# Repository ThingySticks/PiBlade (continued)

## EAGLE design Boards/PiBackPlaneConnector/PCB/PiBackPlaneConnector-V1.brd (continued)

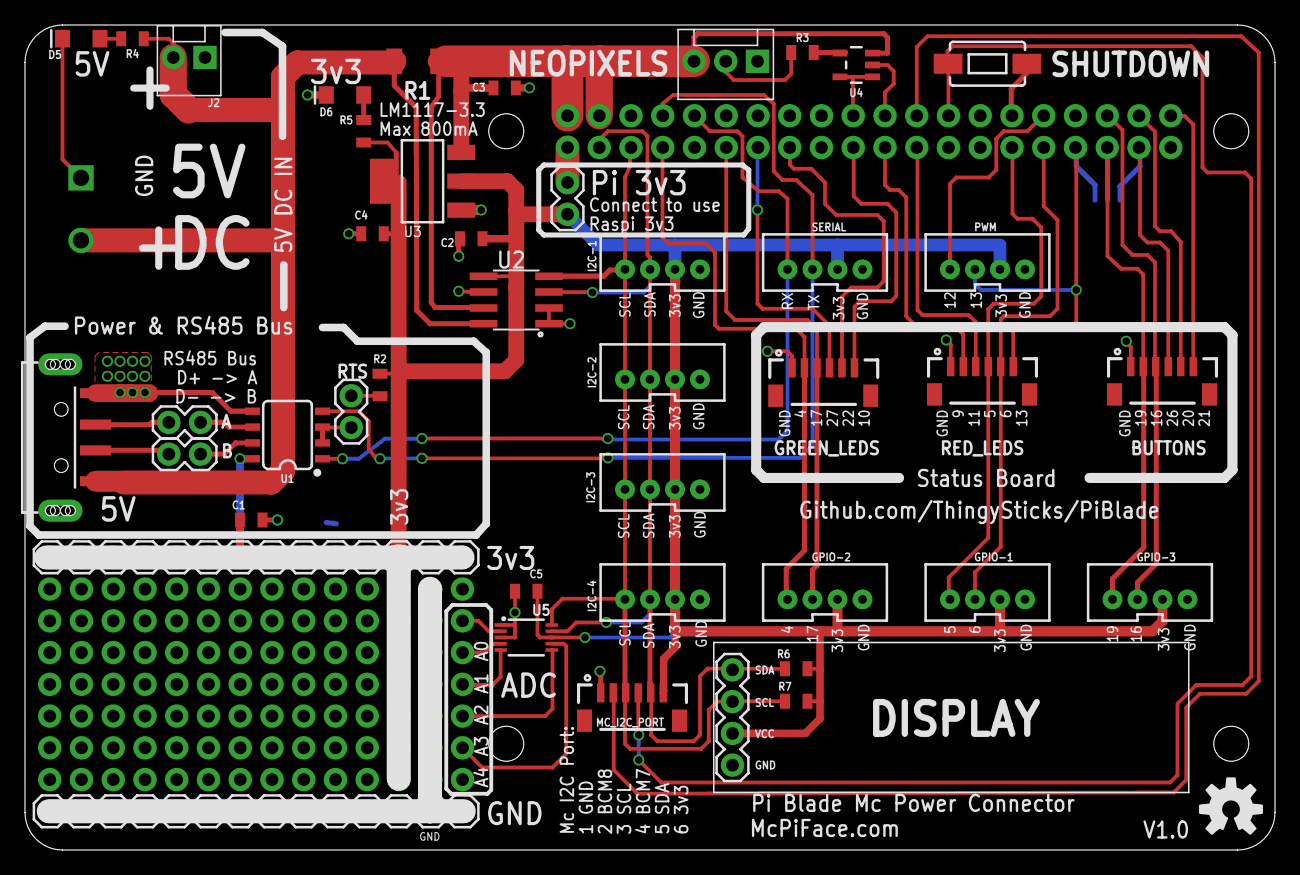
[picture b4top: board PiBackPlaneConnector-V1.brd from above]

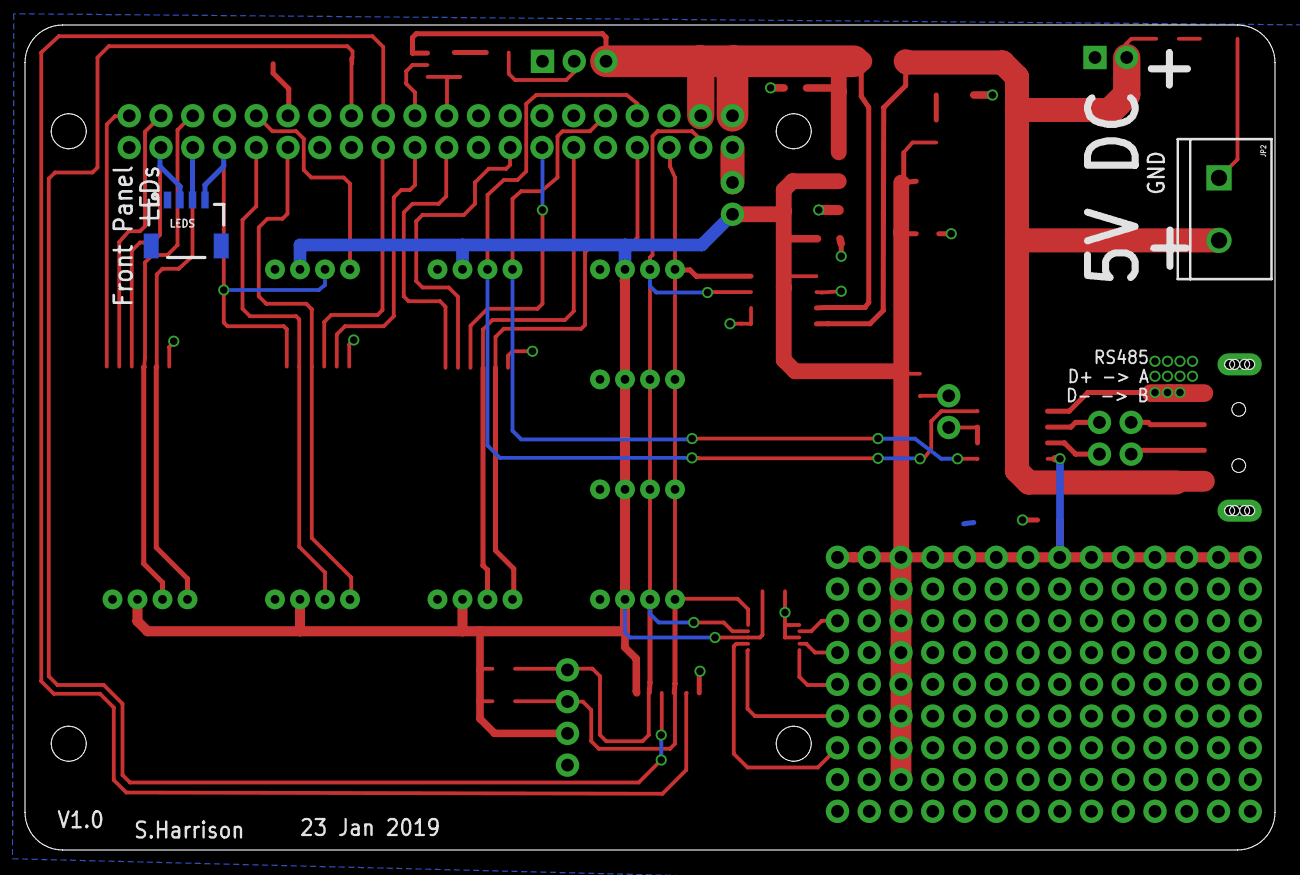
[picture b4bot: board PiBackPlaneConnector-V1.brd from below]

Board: 2 copper layers, 100.0 x 66.0 mm, 55 parts (3 on the bottom side), 43 nets.

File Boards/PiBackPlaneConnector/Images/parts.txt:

Partlist

Exported from PiBackPlaneConnector-V1.brd at 25/01/2019 11:44

EAGLE Version 7.4.0 Copyright (c) 1988-2015 CadSoft

Assembly variant: 

Part        Value                               Package                      Library                Position (mm)         Orientation

A                                               1X02                         SparkFun-Connectors    (-20.955 29.21)       R180
B                                               1X02                         SparkFun-Connectors    (-20.955 26.67)       R180
BUTTONS                                         1X06-1MM                     SparkFun-Connectors    (56 32.4)             R0
C1          0.1uF                               0805                         SparkFun-Capacitors    (-16.9 21.4)          R0
C2          0.1uF                               0805                         SparkFun-Capacitors    (0.7 43.9)            R180
C3          1.0uF                               0805                         SparkFun-Capacitors    (3.37 55.965)         R0
C4          0.1uF                               0805                         SparkFun-Capacitors    (-7.2 44.3)           R180
C5          0.1uF                               0805                         SparkFun-Capacitors    (5.1 15.7)            R180
D5          BLUE                                LED-1206                     SparkFun-LED           (-30.5 59.9)          R180
D6          BLUE                                LED-1206                     SparkFun-LED           (-9.4 55.4)           R180
DISPLAY     DISPLAY0.91_INCH_DISPLAY            I2C_DISPLAY_0.91_INCH        ThingySticks           (20.1 -0.4)           R0
GPIO-1                                          JST-4-PTH-VERT               SparkFun-Connectors    (42 15.6)             R0
GPIO-2                                          JST-4-PTH-VERT               SparkFun-Connectors    (29 15.6)             R0
GPIO-3                                          JST-4-PTH-VERT               SparkFun-Connectors    (55 15.6)             R0
GREEN_LEDS                                      1X06-1MM                     SparkFun-Connectors    (28.9 32.3)           R0
I2C-1                                           JST-4-PTH-VERT               SparkFun-Connectors    (16 42)               R0
I2C-2                                           JST-4-PTH-VERT               SparkFun-Connectors    (16 33.2)             R0
I2C-3                                           JST-4-PTH-VERT               SparkFun-Connectors    (16 24.4)             R0
I2C-4                                           JST-4-PTH-VERT               SparkFun-Connectors    (16 15.6)             R0
J1          CONN_20X2NOSILK                     2X20_NOSILK                  SparkFun-Connectors    (8.4 51.2)            R0
J2                                              MOLEX-1X2                    SparkFun-Connectors    (-20.6 58.4)          R180
J3                                              1X14                         SparkFun-Connectors    (-33.02 18.415)       R0
J4          USB_A_SMT_MALE                      USB-A-SMT-MALE               Tinamous               (-40.3 28)            R0
J7                                              1X02                         SparkFun-Connectors    (8.4 48.4)            R270
J8                                              1X14                         SparkFun-Connectors    (-33.02 -1.905)       R0
J9                                              1X14_NO_SILK                 SparkFun-Connectors    (-33.02 15.875)       R0
J10                                             1X14_NO_SILK                 SparkFun-Connectors    (-33.02 13.335)       R0
J11                                             1X14_NO_SILK                 SparkFun-Connectors    (-33.02 10.795)       R0
J12                                             1X14_NO_SILK                 SparkFun-Connectors    (-33.02 8.255)        R0
J13                                             1X14_NO_SILK                 SparkFun-Connectors    (-33.02 5.715)        R0
J14                                             1X14_NO_SILK                 SparkFun-Connectors    (-33.02 3.175)        R0
J15                                             1X14_NO_SILK                 SparkFun-Connectors    (-33.02 0.635)        R0
JP2                                             SCREWTERMINAL-5MM-2@1        SparkFun-Connectors    (-30.52 48.77)        MR270
LEDS                                            1X04_1MM_RA                  SparkFun-Connectors    (52.1 47)             MR0
MC_I2C_PORT                                     1X06-1MM                     SparkFun-Connectors    (13.6 6.3)            R0
NEOPIXELS                                       MOLEX-1X3                    SparkFun-Connectors    (23.6 58.1)           R180
PWM                                             JST-4-PTH-VERT               SparkFun-Connectors    (42 42)               R0
R1          0.1                                 1210                         SparkFun-Resistors     (-3.7 58.1)           R0
R2          10k                                 0805                         SparkFun-Resistors     (-6.6 32.2)           R90
R3                                              0805                         SparkFun-Resistors     (27.2 58.8)           R0
R4          1k5                                 0805                         SparkFun-Resistors     (-26.4 59.9)          R180
R5          1k                                  0805                         SparkFun-Resistors     (-7.9 52.5)           R90
R6          10k                                 0805                         SparkFun-Resistors     (26.7 9.5)            R180
R7          10k                                 0805                         SparkFun-Resistors     (26.7 6.9)            R180
RED_LEDS                                        1X06-1MM                     SparkFun-Connectors    (41.6 32.4)           R0
RTS                                             1X02                         SparkFun-Connectors    (-8.9 28.8)           R90
SERIAL                                          JST-4-PTH-VERT               SparkFun-Connectors    (29 42)               R0
SHUTDOWN    MOMENTARY-SWITCH-SPST-SMD-6.0X3.5MM TACTILE_SWITCH_SMD_6.0X3.5MM ThingySticks           (42 57.9)             R180
U1           MAX3485CSA                         SO08                         SparkFun-IC-Comms      (-14 28.2)            R90
U2          INA219AIDCNRSOIC                    SO08                         INA219AIDCNR           (4.3 39)              R90
U3                                              SOT223                       SparkFun-PowerIC       (-3.2 48.5)           R90
U4          SN74AHC1G125                        SOT23-5                      SparkFun-IC-Logic      (31.5 57.8)           R90
U5          ADS1015                             MSOP10                       SparkFun-IC-Conversion (5.1 12)              R270

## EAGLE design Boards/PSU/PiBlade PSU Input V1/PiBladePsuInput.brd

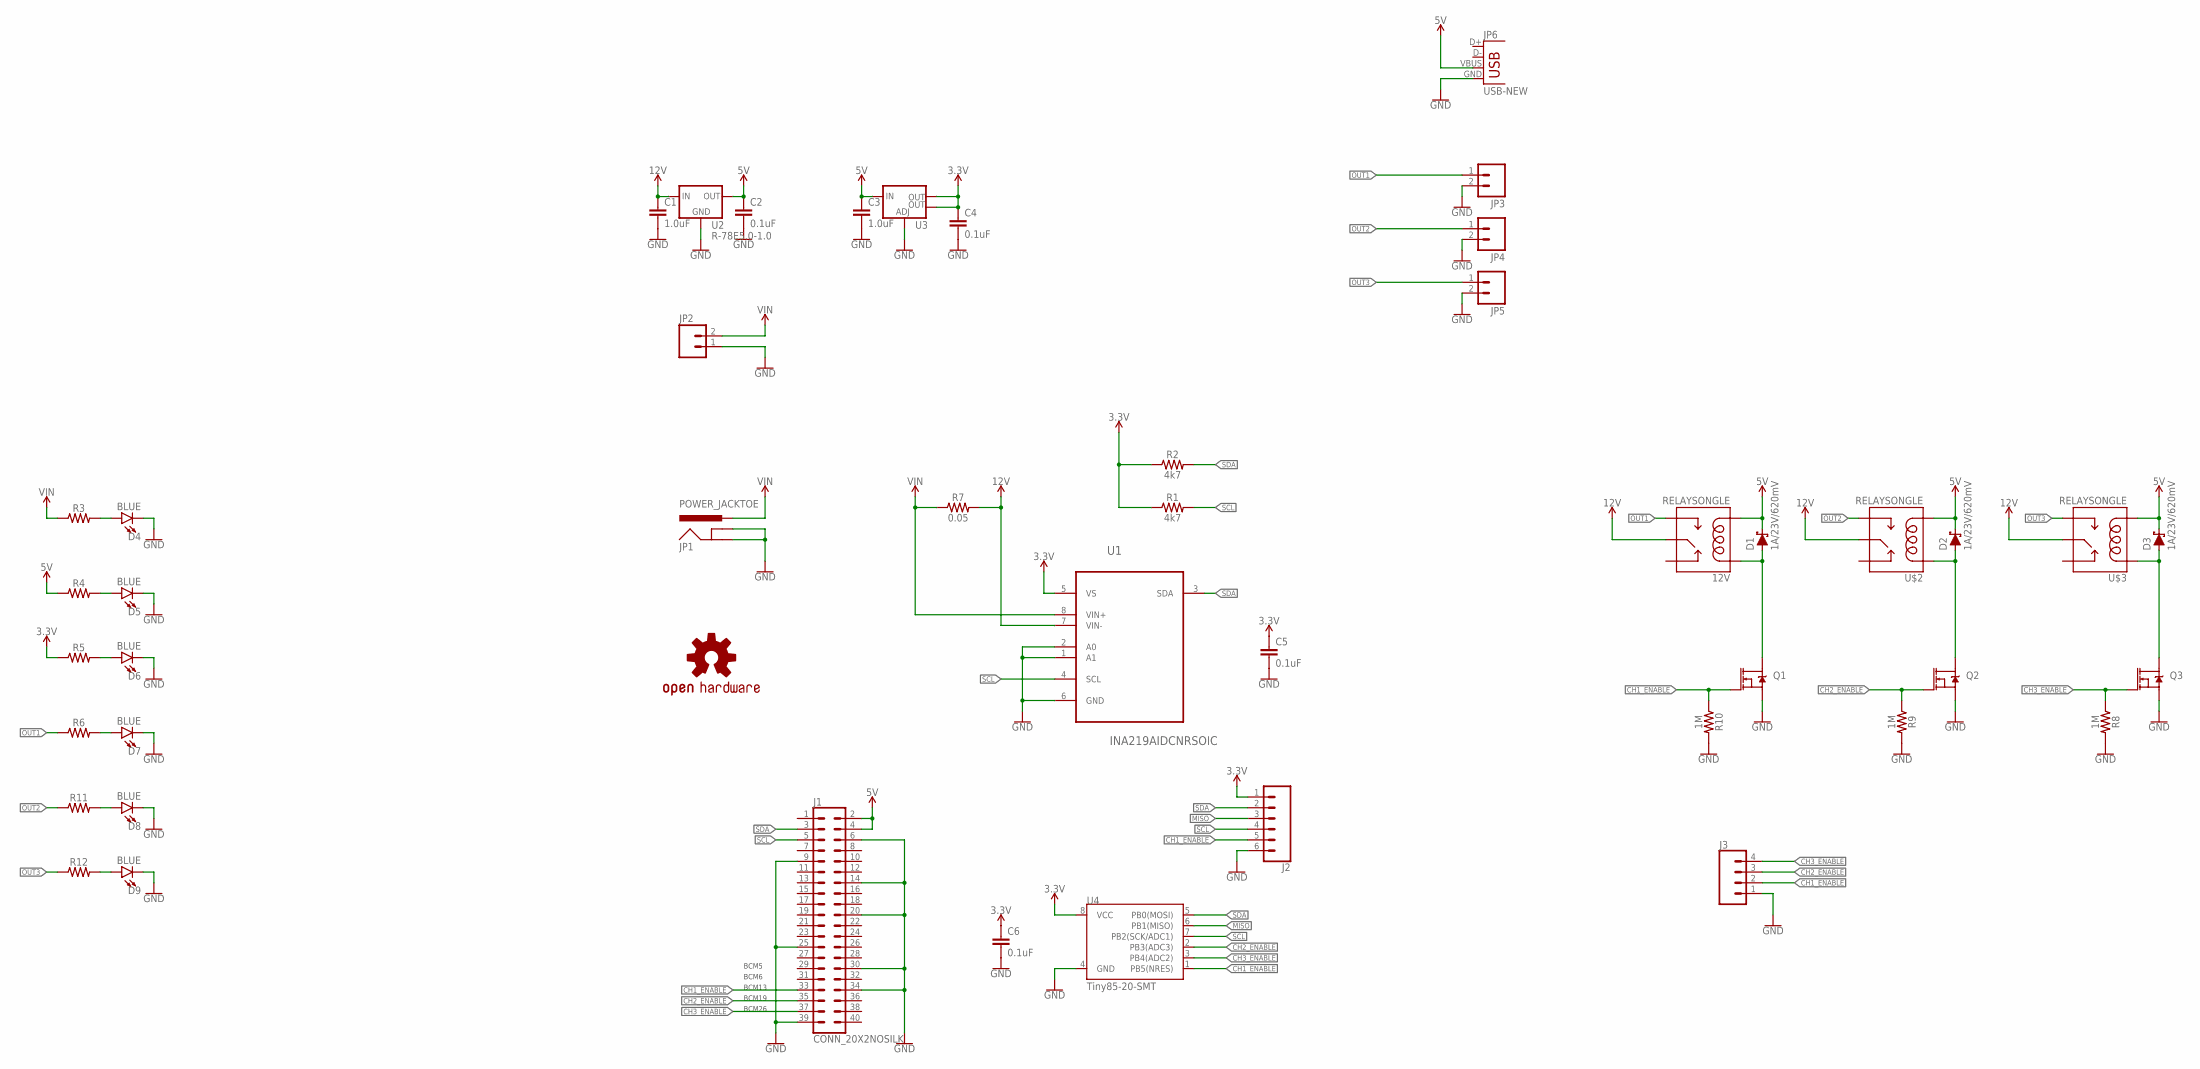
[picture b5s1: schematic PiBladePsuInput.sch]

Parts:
12V: RELAYSONGLE; SRD-5VDC-SL-C
C1, C3: 1.0uF; 0805
C2, C4, C5, C6: 0.1uF; 0805
D1, D2, D3: 1A/23V/620mV; SOD-323
D4, D5, D6, D7, D8, D9: BLUE; LED-1206
J1: CONN_20X2NOSILK; 2X20_NOSILK
J2: CONN_06SMD-1MM; 1X06-1MM
J3: CONN_04SMD2; 1X04_1MM_RA
JP1: POWER_JACKTOE; POWER_JACK_SMD_OVERPASTE_TOE
JP2, JP3, JP4, JP5: M025MM; SCREWTERMINAL-5MM-2
JP6: USB-NEW; USB-A-VERTICAL
LOGO1: OSHW-LOGOM; OSHW-LOGO-M
Q1, Q2, Q3: 220mA/50V/3.5Ω; SOT23-3
R1, R2: 4k7; 0805
R3, R4, R5, R6, R11, R12: 0805
R7: 0.05; 2512
R8, R9, R10: 1M; 0805
U1: INA219AIDCNRSOIC; SO08
U2: R-78E5.0-1.0; DC-DC_CONVERTER_78XX
U3: V_REG_LM1117SOT223; SOT223
U4: Tiny85-20-SMT; SO08-EIAJ
U$2, U$3: RELAYSONGLE; SRD-5VDC-SL-C

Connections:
3.3V: C4.1, C5.1, C6.1, J2.1, R1.1, R2.1, R5.1, U1.5 (VS), U3.2 (OUT), U3.4 (OUT), U4.8 (VCC)
5V: 12V.COIL2, C2.1, C3.1, D1.C, D2.C, D3.C, J1.2, J1.4, JP6.VBUS, R4.1, U2.VOUT (OUT), U3.3 (IN), U$2.COIL2, U$3.COIL2
12V: 12V.COMMON (MAIN), C1.1, R7.P$2 (2), U1.7 (VIN-), U2.VIN (IN), U$2.COMMON (MAIN), U$3.COMMON (MAIN)
CH1_ENABLE: J1.33, J2.5, J3.2, Q1.1 (G), R10.1, U4.1 (PB5(NRES))
CH2_ENABLE: J1.35, J3.3, Q2.1 (G), R9.1, U4.2 (PB3(ADC3))
CH3_ENABLE: J1.37, J3.4, Q3.1 (G), R8.1, U4.3 (PB4(ADC2))
GND: C1.2, C2.2, C3.2, C4.2, C5.2, C6.2, D4.C, D5.C, D6.C, D7.C, D8.C, D9.C, J1.6, J1.9, J1.14, J1.20, J1.25, J1.30, J1.34, J1.39, J2.6, J3.1, JP1.GND (GNDBREAK), JP1.P$4 (GND), JP2.1, JP3.2, JP4.2, JP5.2, JP6.GND, Q1.2 (S), Q2.2 (S), Q3.2 (S), R8.2, R9.2, R10.2, U1.1 (A1), U1.2 (A0), U1.6 (GND), U2.GND, U3.1 (ADJ), U4.4 (GND)
MISO: J2.3, U4.6 (PB1(MISO))
unnamed: D4.A, R3.2
unnamed: D6.A, R5.2
unnamed: D7.A, R6.2
unnamed: D5.A, R4.2
unnamed: D8.A, R11.2
unnamed: D9.A, R12.2
unnamed: D3.A, Q3.3 (D), U$3.COIL1
unnamed: D2.A, Q2.3 (D), U$2.COIL1
unnamed: 12V.COIL1, D1.A, Q1.3 (D)
OUT1: 12V.OPEN (NO), JP3.1, R6.1
OUT2: JP4.1, R11.1, U$2.OPEN (NO)
OUT3: JP5.1, R12.1, U$3.OPEN (NO)
SCL: J1.5, J2.4, R1.2, U1.4 (SCL), U4.7 (PB2(SCK/ADC1))
SDA: J1.3, J2.2, R2.2, U1.3 (SDA), U4.5 (PB0(MOSI))
VIN: JP1.VIN0 (PWR), JP2.2, R3.1, R7.P$1 (1), U1.8 (VIN+)

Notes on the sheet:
BCM13
BCM6
BCM5
BCM26
BCM19

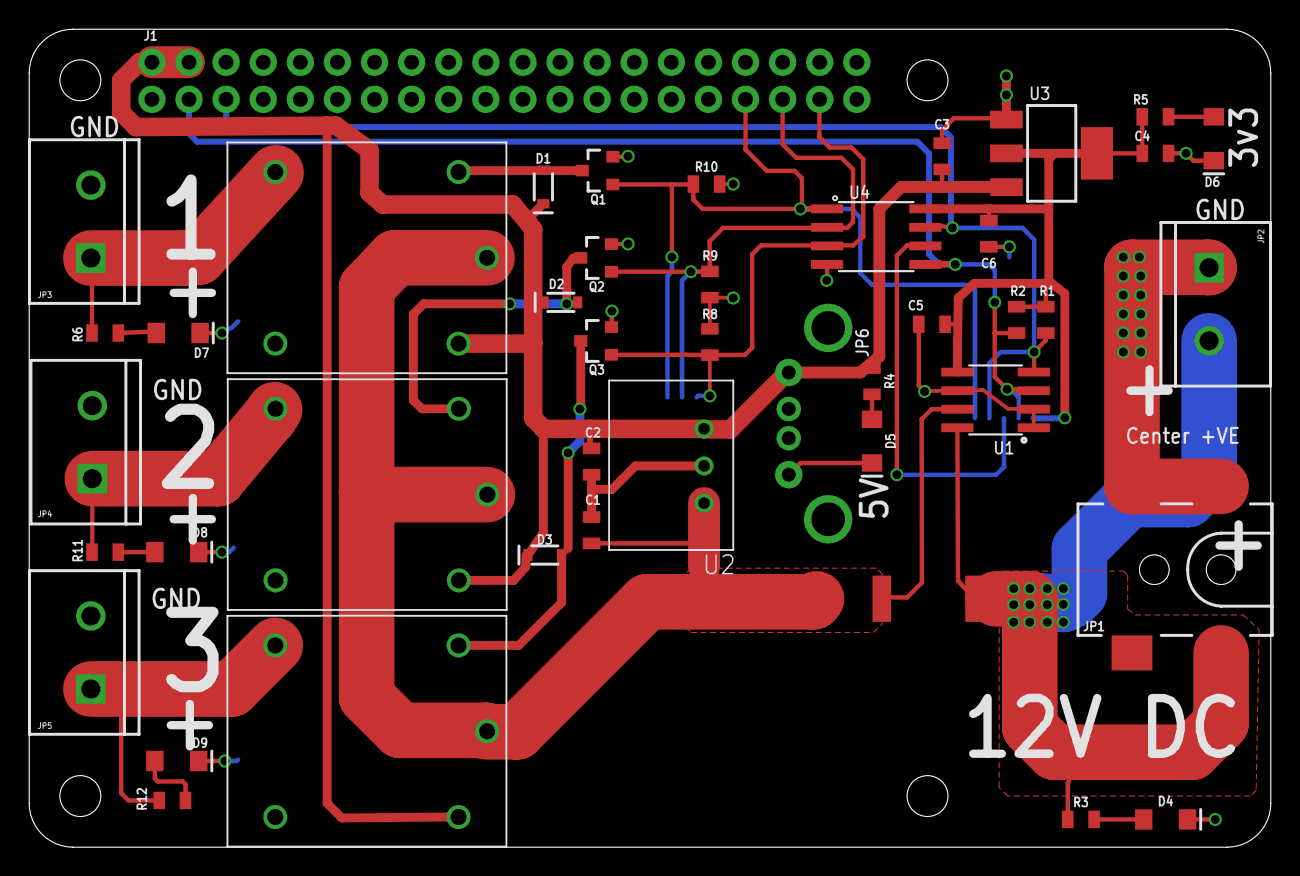
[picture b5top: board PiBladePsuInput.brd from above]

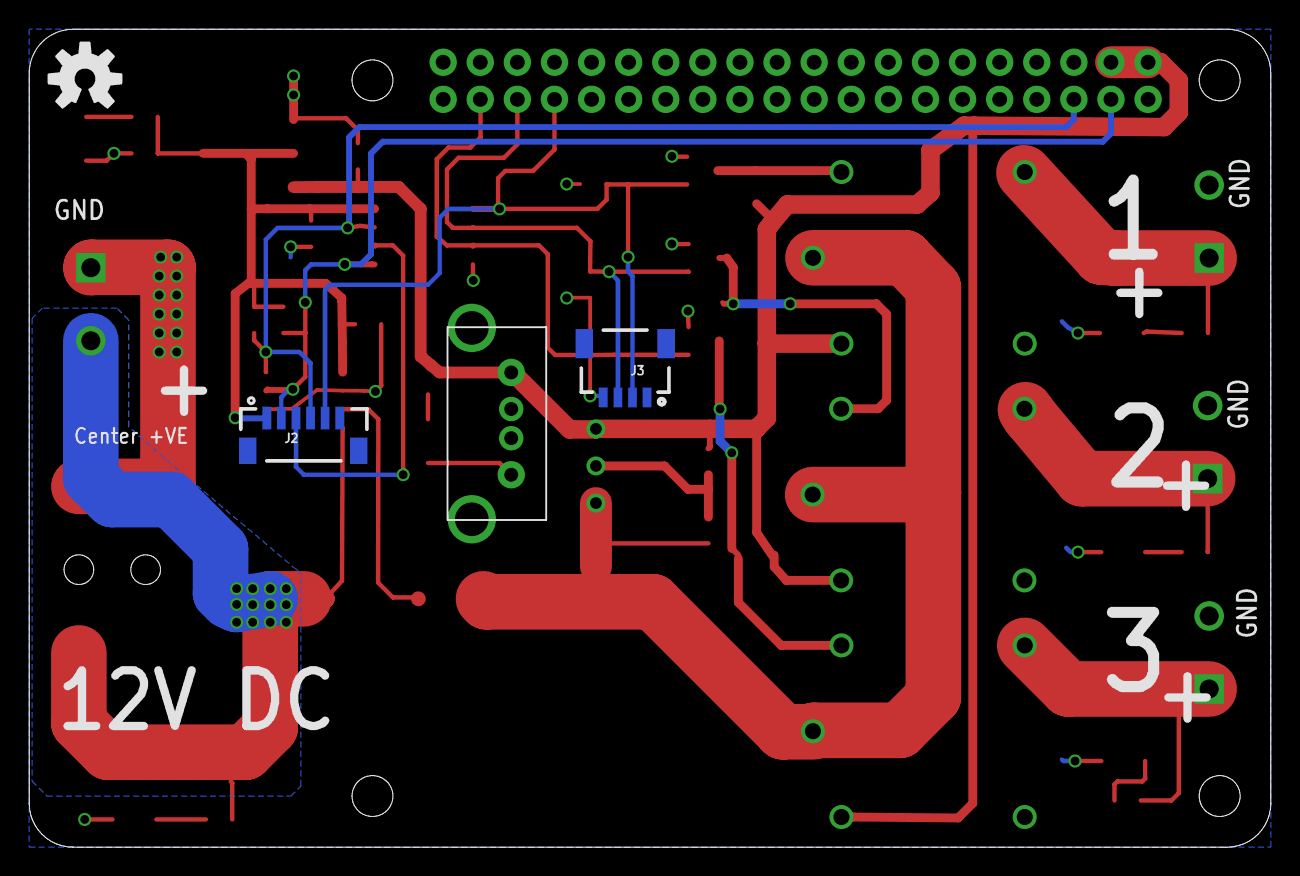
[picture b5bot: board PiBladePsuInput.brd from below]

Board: 2 copper layers, 85.0 x 56.0 mm, 47 parts (2 on the bottom side), 23 nets.

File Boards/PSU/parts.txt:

Partlist

Exported from PiBladePsuInput.brd at 25/01/2019 11:47

EAGLE Version 7.4.0 Copyright (c) 1988-2015 CadSoft

Assembly variant: 

Part     Value            Package                      Library               Position (mm)         Orientation

12V      RELAYSONGLE      SRD-5VDC-SL-C                ThingySticks          (23.12 40.35)         R0
C1       1.0uF            0805                         SparkFun-Capacitors   (38.5 21.7)           R90
C2       0.1uF            0805                         SparkFun-Capacitors   (38.5 26.4)           R270
C3       1.0uF            0805                         SparkFun-Capacitors   (62.5 47.3)           R90
C4       0.1uF            0805                         SparkFun-Capacitors   (77.1 47.5)           R0
C5       0.1uF            0805                         SparkFun-Capacitors   (61.8 35.8)           R180
C6       0.1uF            0805                         SparkFun-Capacitors   (65.7 42)             R270
D1       1A/23V/620mV     SOD-323                      SparkFun-DiscreteSemi (35.2 45.2)           R90
D2       1A/23V/620mV     SOD-323                      SparkFun-DiscreteSemi (36.4 37.3)           R0
D3       1A/23V/620mV     SOD-323                      SparkFun-DiscreteSemi (35.3 20)             R0
D4       BLUE             LED-1206                     SparkFun-LED          (77.8 1.9)            R0
D5       BLUE             LED-1206                     SparkFun-LED          (57.7 27.8)           R270
D6       BLUE             LED-1206                     SparkFun-LED          (81.1 48.5)           R270
D7       BLUE             LED-1206                     SparkFun-LED          (10.2 35.2)           R0
D8       BLUE             LED-1206                     SparkFun-LED          (10.1 20.2)           R0
D9       BLUE             LED-1206                     SparkFun-LED          (10.1 5.9)            R0
J1       CONN_20X2NOSILK  2X20_NOSILK                  SparkFun-Connectors   (8.4 51.2)            R0
J2                        1X06-1MM                     SparkFun-Connectors   (66.2 28.1)           MR0
J3                        1X04_1MM_RA                  SparkFun-Connectors   (44.2 30.8)           MR180
JP1      POWER_JACKTOE    POWER_JACK_SMD_OVERPASTE_TOE SparkFun-Connectors   (81.6 19)             R180
JP2                       SCREWTERMINAL-5MM-2          SparkFun-Connectors   (80.78 39.67)         R270
JP3                       SCREWTERMINAL-5MM-2          SparkFun-Connectors   (4.22 40.33)          R90
JP4                       SCREWTERMINAL-5MM-2          SparkFun-Connectors   (4.32 25.23)          R90
JP5                       SCREWTERMINAL-5MM-2          SparkFun-Connectors   (4.22 10.83)          R90
JP6      USB-NEW          USB-A-VERTICAL               Tinamous              (54.7 29)             R180
Q1       220mA/50V/3.5?   SOT23-3                      SparkFun-DiscreteSemi (38.96 46.32)         R90
Q2       220mA/50V/3.5?   SOT23-3                      SparkFun-DiscreteSemi (38.86 40.34)         R90
Q3       220mA/50V/3.5?   SOT23-3                      SparkFun-DiscreteSemi (38.86 34.66)         R90
R1       4k7              0805                         SparkFun-Resistors    (69.6 36.1)           R270
R2       4k7              0805                         SparkFun-Resistors    (67.6 36.1)           R270
R3                        0805                         SparkFun-Resistors    (72 1.9)              R0
R4                        0805                         SparkFun-Resistors    (57.7 31.9)           R270
R5                        0805                         SparkFun-Resistors    (77.1 50)             R0
R6                        0805                         SparkFun-Resistors    (5.2 35.2)            R0
R7       0.05             2512                         SparkFun-Resistors    (61.54 17.01)         R180
R8       1M               0805                         SparkFun-Resistors    (46.6 34.59)          R90
R9       1M               0805                         SparkFun-Resistors    (46.6 38.52)          R270
R10      1M               0805                         SparkFun-Resistors    (46.37 45.4)          R0
R11                       0805                         SparkFun-Resistors    (5.2 20.2)            R0
R12                       0805                         SparkFun-Resistors    (9.8 3.2)             R0
U$2      RELAYSONGLE      SRD-5VDC-SL-C                ThingySticks          (23.14 24.14)         R0
U$3      RELAYSONGLE      SRD-5VDC-SL-C                ThingySticks          (23.12 7.94)          R0
U1       INA219AIDCNRSOIC SO08                         INA219AIDCNR          (66.16 30.62)         R90
U2       R-78E5.0-1.0     DC-DC_CONVERTER_78XX         SparkFun-IC-Power     (46.2 26.1)           R90
U3                        SOT223                       SparkFun-PowerIC      (70 47.5)             R270
U4       Tiny85-20-SMT    SO08-EIAJ                    SparkFun-DigitalIC    (58 41.8)             R270

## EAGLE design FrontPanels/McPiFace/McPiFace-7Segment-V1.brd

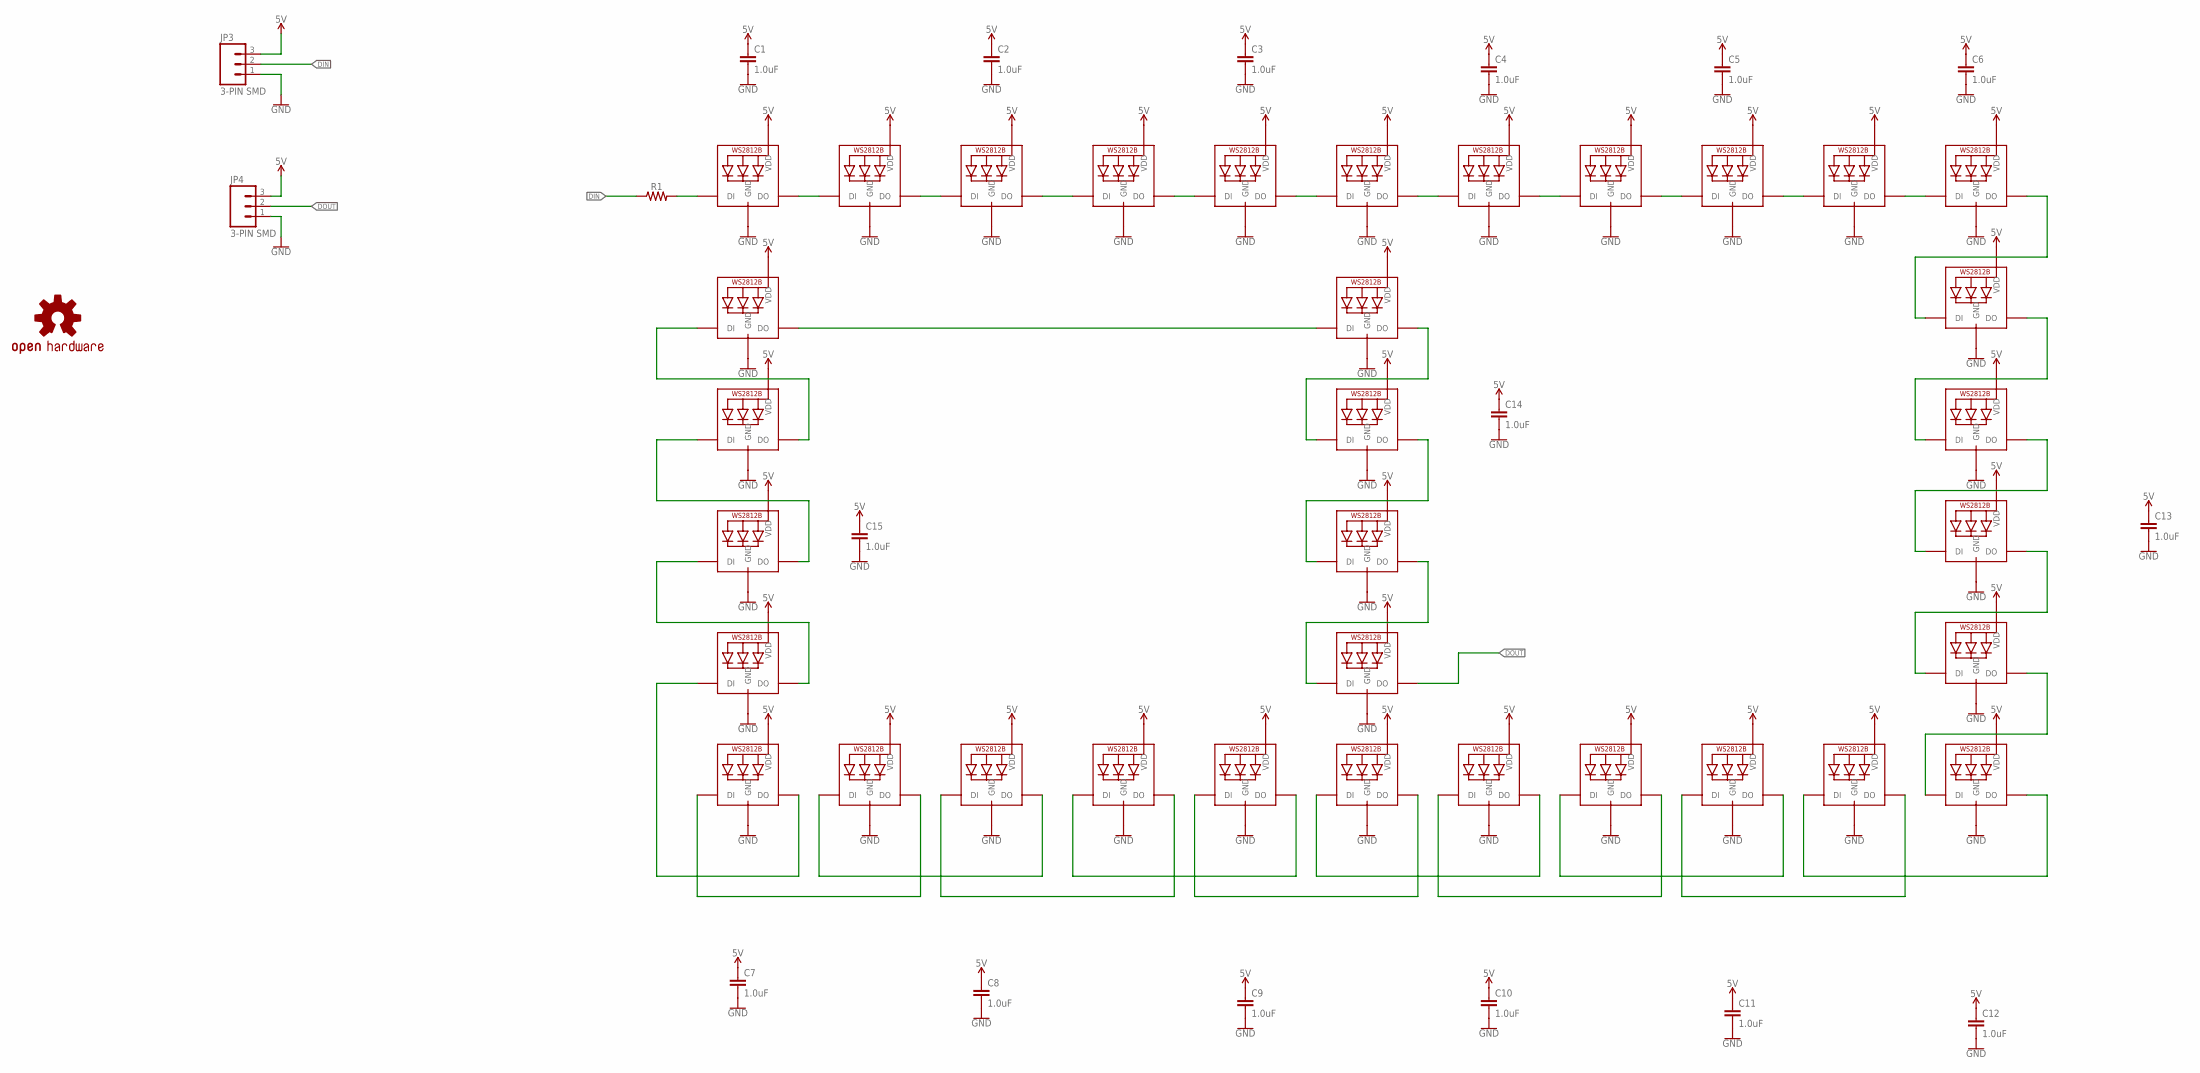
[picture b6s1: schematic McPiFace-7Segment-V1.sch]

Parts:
C1, C2, C3, C4, C5, C6, C7, C8, C9, C10, C11, C12, C13, C14, C15: 1.0uF; 0805-CAP
JP3, JP4: 3-PIN SMD; JST-3-SMD
LED1, LED2, LED3, LED4, LED5, LED6, LED7, LED8, LED9, LED10, LED11, LED12, LED13, LED14, LED15, LED16, LED17, LED18, LED19, LED20, LED21, LED22, LED23, LED24, LED25, LED26, LED27, LED28, LED29, LED30, LED31, LED32, LED33, LED34: WS2812B5050; WS2812B
LOGO1: OSHW-LOGOL; OSHW-LOGO-L
R1: 0805

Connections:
5V: C1.1, C2.1, C3.1, C4.1, C5.1, C6.1, C7.1, C8.1, C9.1, C10.1, C11.1, C12.1, C13.1, C14.1, C15.1, JP3.3, JP4.3, LED1.1-VDD (VDD), LED2.1-VDD (VDD), LED3.1-VDD (VDD), LED4.1-VDD (VDD), LED5.1-VDD (VDD), LED6.1-VDD (VDD), LED7.1-VDD (VDD), LED8.1-VDD (VDD), LED9.1-VDD (VDD), LED10.1-VDD (VDD), LED11.1-VDD (VDD), LED12.1-VDD (VDD), LED13.1-VDD (VDD), LED14.1-VDD (VDD), LED15.1-VDD (VDD), LED16.1-VDD (VDD), LED17.1-VDD (VDD), LED18.1-VDD (VDD), LED19.1-VDD (VDD), LED20.1-VDD (VDD), LED21.1-VDD (VDD), LED22.1-VDD (VDD), LED23.1-VDD (VDD), LED24.1-VDD (VDD), LED25.1-VDD (VDD), LED26.1-VDD (VDD), LED27.1-VDD (VDD), LED28.1-VDD (VDD), LED29.1-VDD (VDD), LED30.1-VDD (VDD), LED31.1-VDD (VDD), LED32.1-VDD (VDD), LED33.1-VDD (VDD), LED34.1-VDD (VDD)
DIN: JP3.2, R1.1
DOUT: JP4.2, LED15.2-DOUT (DO)
GND: C1.2, C2.2, C3.2, C4.2, C5.2, C6.2, C7.2, C8.2, C9.2, C10.2, C11.2, C12.2, C13.2, C14.2, C15.2, JP3.1, JP4.1, LED1.3-GND (GND), LED2.3-GND (GND), LED3.3-GND (GND), LED4.3-GND (GND), LED5.3-GND (GND), LED6.3-GND (GND), LED7.3-GND (GND), LED8.3-GND (GND), LED9.3-GND (GND), LED10.3-GND (GND), LED11.3-GND (GND), LED12.3-GND (GND), LED13.3-GND (GND), LED14.3-GND (GND), LED15.3-GND (GND), LED16.3-GND (GND), LED17.3-GND (GND), LED18.3-GND (GND), LED19.3-GND (GND), LED20.3-GND (GND), LED21.3-GND (GND), LED22.3-GND (GND), LED23.3-GND (GND), LED24.3-GND (GND), LED25.3-GND (GND), LED26.3-GND (GND), LED27.3-GND (GND), LED28.3-GND (GND), LED29.3-GND (GND), LED30.3-GND (GND), LED31.3-GND (GND), LED32.3-GND (GND), LED33.3-GND (GND), LED34.3-GND (GND)
unnamed: LED1.2-DOUT (DO), LED2.4-DIN (DI)
unnamed: LED1.4-DIN (DI), R1.2
unnamed: LED2.2-DOUT (DO), LED3.4-DIN (DI)
unnamed: LED3.2-DOUT (DO), LED4.4-DIN (DI)
unnamed: LED4.2-DOUT (DO), LED5.4-DIN (DI)
unnamed: LED5.2-DOUT (DO), LED6.4-DIN (DI)
unnamed: LED6.2-DOUT (DO), LED7.4-DIN (DI)
unnamed: LED7.2-DOUT (DO), LED8.4-DIN (DI)
unnamed: LED8.2-DOUT (DO), LED9.4-DIN (DI)
unnamed: LED9.2-DOUT (DO), LED10.4-DIN (DI)
unnamed: LED10.2-DOUT (DO), LED11.4-DIN (DI)
unnamed: LED11.2-DOUT (DO), LED17.4-DIN (DI)
unnamed: LED17.2-DOUT (DO), LED18.4-DIN (DI)
unnamed: LED18.2-DOUT (DO), LED19.4-DIN (DI)
unnamed: LED19.2-DOUT (DO), LED20.4-DIN (DI)
unnamed: LED20.2-DOUT (DO), LED21.4-DIN (DI)
unnamed: LED21.2-DOUT (DO), LED22.4-DIN (DI)
unnamed: LED22.2-DOUT (DO), LED23.4-DIN (DI)
unnamed: LED23.2-DOUT (DO), LED24.4-DIN (DI)
unnamed: LED24.2-DOUT (DO), LED25.4-DIN (DI)
unnamed: LED16.4-DIN (DI), LED25.2-DOUT (DO)
unnamed: LED16.2-DOUT (DO), LED26.4-DIN (DI)
unnamed: LED26.2-DOUT (DO), LED27.4-DIN (DI)
unnamed: LED27.2-DOUT (DO), LED28.4-DIN (DI)
unnamed: LED28.2-DOUT (DO), LED29.4-DIN (DI)
unnamed: LED29.2-DOUT (DO), LED30.4-DIN (DI)
unnamed: LED30.2-DOUT (DO), LED31.4-DIN (DI)
unnamed: LED31.2-DOUT (DO), LED32.4-DIN (DI)
unnamed: LED32.2-DOUT (DO), LED33.4-DIN (DI)
unnamed: LED33.2-DOUT (DO), LED34.4-DIN (DI)
unnamed: LED12.4-DIN (DI), LED34.2-DOUT (DO)
unnamed: LED12.2-DOUT (DO), LED13.4-DIN (DI)
unnamed: LED13.2-DOUT (DO), LED14.4-DIN (DI)
unnamed: LED14.2-DOUT (DO), LED15.4-DIN (DI)

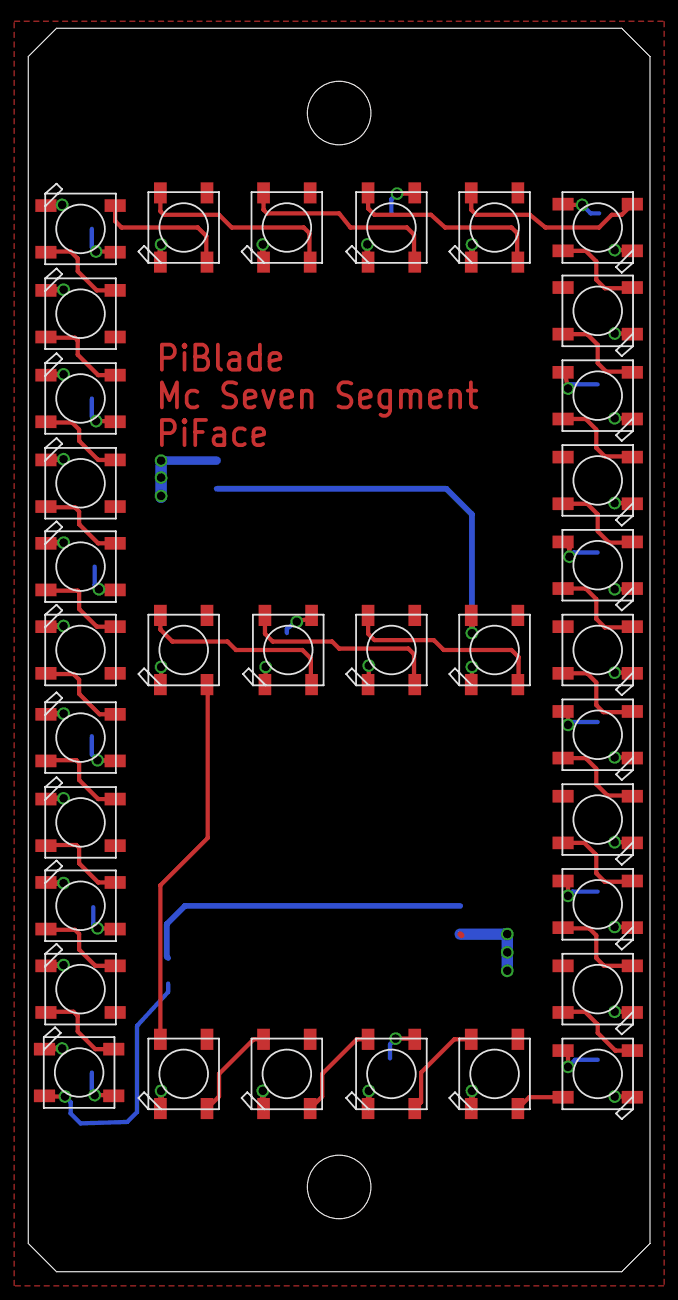
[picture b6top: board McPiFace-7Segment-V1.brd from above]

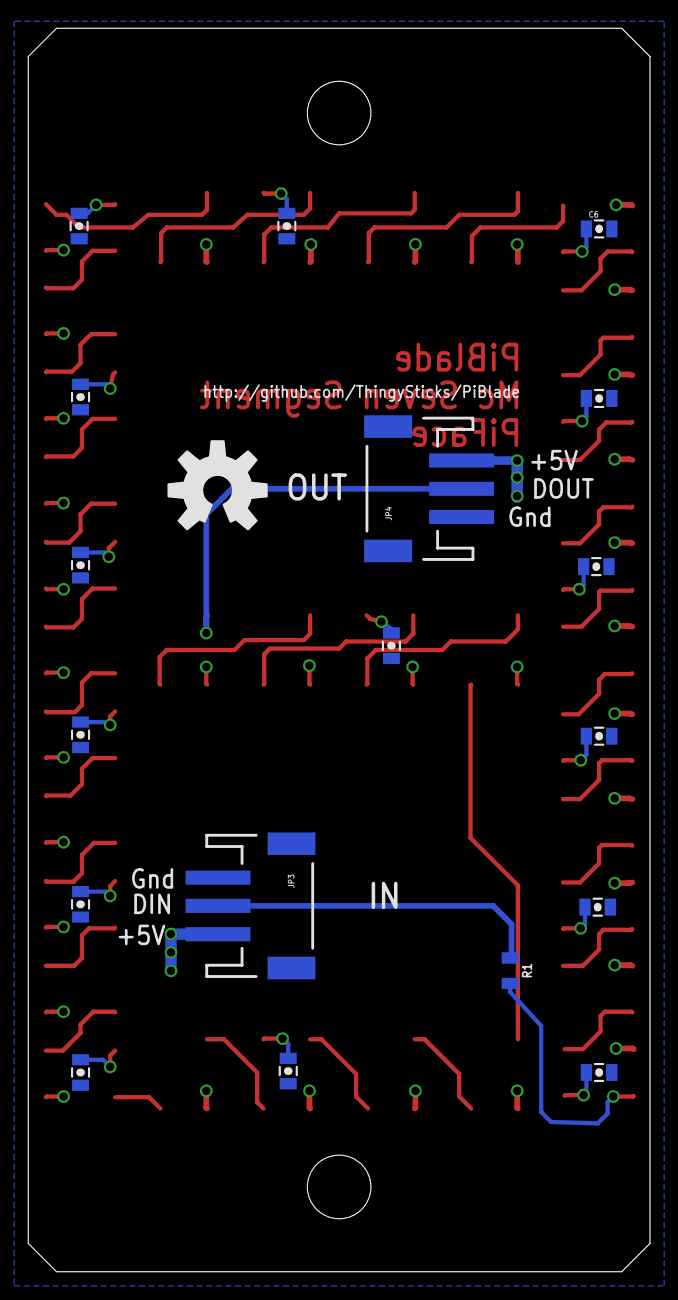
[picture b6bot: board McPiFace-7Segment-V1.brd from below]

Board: 2 copper layers, 44.0 x 88.0 mm, 53 parts (19 on the bottom side), 38 nets.
